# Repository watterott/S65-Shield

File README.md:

# S65-Shield
The S65-Shield is a plug-on module with color TFT-Display (176x132), microSD socket and rotary encoder for Arduino.

* Color-Display (176x132)
* Rotary-Encoder
* microSD Socket (SPI)
* Open-Source and released under the [Creative Commons Attribution Share-Alike License](https://creativecommons.org/licenses/by-sa/4.0/).
* **[Documentation on learn.watterott.com](https://learn.watterott.com)**

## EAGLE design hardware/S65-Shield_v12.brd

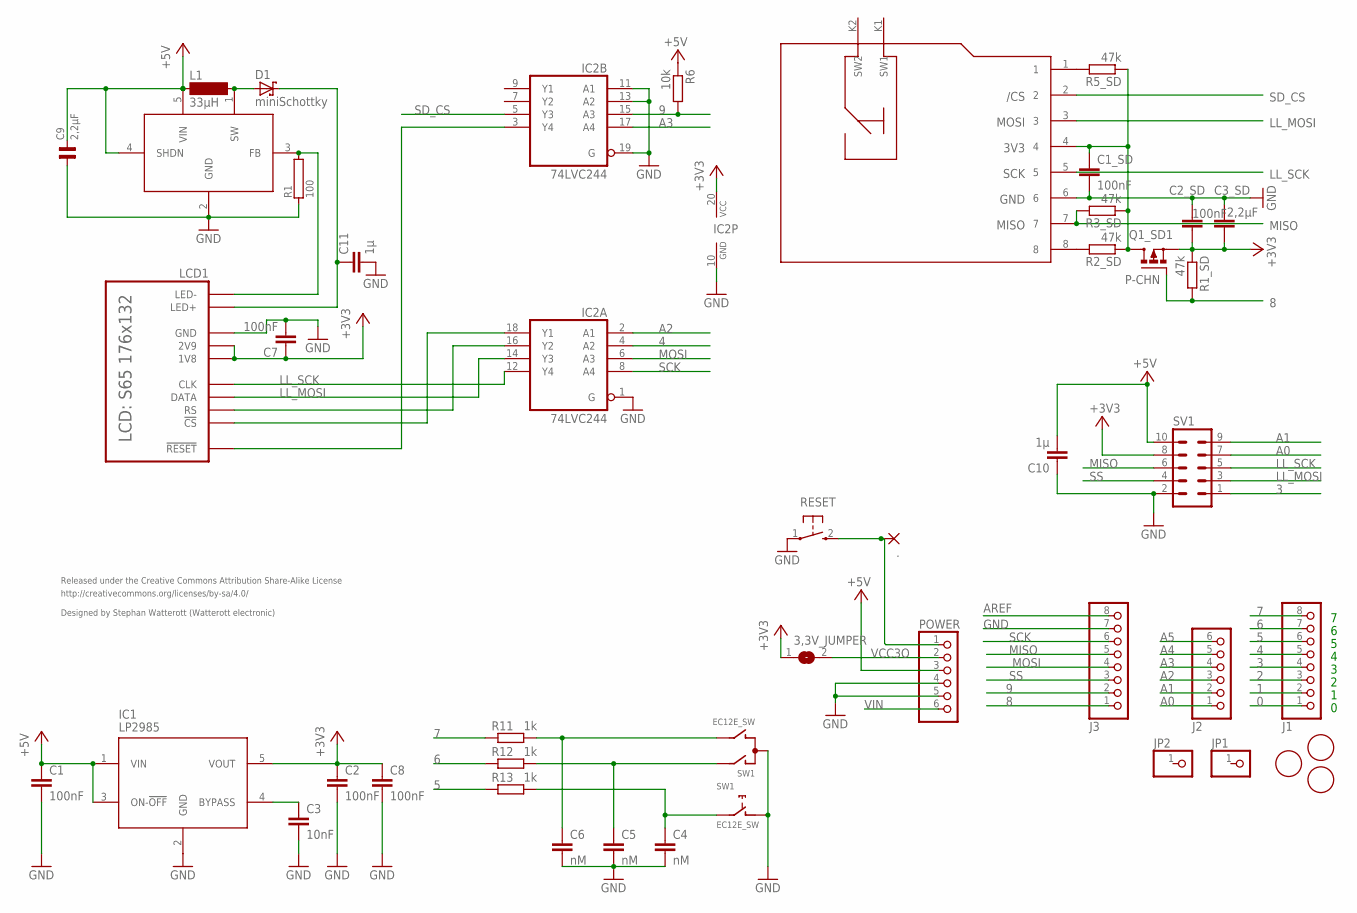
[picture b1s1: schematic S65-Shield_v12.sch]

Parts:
3,3V_JUMPER: SJ
.: SMD2; SMD1,27-2,54
C1, C1_SD, C2, C2_SD, C7: 100nF; C0603
C3: 10nF; C0603
C3_SD: 2,2µF; C0805
C4, C5, C6: nM; C0603
C8: 100nF; C0805
C9: 2,2µF; 0805
C10, C11: 1µ; C0603
D1: miniSchottky; D0603
IC1: LP2985; SOT23-5
IC2: 74LVC244; SO20W
J1, J3: PINHD-1X8; 1X08
J2: PINHD-1X6; 1X06
JP1, JP2: PINHD-1X1; 1X01
L1: 33µH; MS42
LCD1: S65
POWER: PINHD-1X6; 1X06
Q1_SD1: P-CHN; MICRO3
R1: 100; 0603
R1_SD, R2_SD, R3_SD, R5_SD: 47k; R0603
R6: 10k; R0603
R11, R12, R13: 1k; R0603
RESET: TAST_SMD1; SMD_TASTER
SD: MICRO-SD
SV1: ML10
SW1: EC12E_SW; ALPS_EC12E_SW
U$1, U$2, U$3: FIDUCIALMOUNT; FIDUCIA-MOUNT
U$4: LM2705; SOT23-5

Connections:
0: J1.1
1: J1.2
2: J1.3
3: J1.4, SV1.1
4: IC2.4 (A2), J1.5
5: J1.6, R13.1
6: J1.7, R12.1
7: J1.8, R11.1
8: J3.1, Q1_SD1.1 (G), R1_SD.2
9: IC2.15 (A3), J3.2, R6.2
+3V3: 3,3V_JUMPER.1, C2.1, C2_SD.2, C3_SD.2, C7.1, C8.1, IC1.5 (VOUT), IC2.20 (VCC), LCD1.1V8, LCD1.2V9, Q1_SD1.2 (S), R1_SD.1, SV1.8
+5V: C1.1, C9.2, C10.2, IC1.1 (VIN), IC1.3 (ON-!OFF), L1.1, POWER.3, R6.1, SV1.10, U$4.4 (SHDN), U$4.5 (VIN)
A0: J2.1, SV1.7
A1: J2.2, SV1.9
A2: IC2.2 (A1), J2.3
A3: IC2.17 (A4), J2.4
A4: J2.5
A5: J2.6
AREF: J3.8
GND: C1.2, C1_SD.2, C2.2, C2_SD.1, C3.2, C3_SD.1, C4.2, C5.2, C6.2, C7.2, C8.2, C9.1, C10.1, C11.2, IC1.2 (GND), IC2.1 (G), IC2.10 (GND), IC2.11 (A1), IC2.13 (A2), IC2.19 (G), J3.7, LCD1.GND, POWER.4, POWER.5, R1.1, RESET.1, SD.6, SV1.2, SW1.C, SW1.D (1), U$4.2 (GND)
LED+: C11.1, D1.1 (C), LCD1.LED+
LED-: LCD1.LED-, R1.2, U$4.3 (FB)
LL_MOSI: IC2.14 (Y3), LCD1.DATA, SD.3, SV1.3
LL_SCK: IC2.12 (Y4), LCD1.CLK, SD.5, SV1.5
MISO: J3.5, R3_SD.2, SD.7, SV1.6
MOSI: IC2.6 (A3), J3.4
unnamed: R5_SD.2, SD.1
unnamed: IC2.16 (Y2), LCD1.RS
unnamed: IC2.18 (Y1), LCD1.CS (!CS)
unnamed: IC2.3 (Y4), LCD1.RESET (!RESET)
unnamed: D1.2 (A), L1.2, U$4.1 (SW)
unnamed: C4.1, R13.2, SW1.E (2)
unnamed: C5.1, R12.2, SW1.A
unnamed: C6.1, R11.2, SW1.B
unnamed: C3.1, IC1.4 (BYPASS)
unnamed: ..1, POWER.1, RESET.2 (S)
unnamed: R2_SD.2, SD.8
SCK: IC2.8 (A4), J3.6
SD_3V3: C1_SD.1, Q1_SD1.3 (D), R2_SD.1, R3_SD.1, R5_SD.1, SD.4
SD_CS: IC2.5 (Y3), SD.2
SS: J3.3, SV1.4
VCC3O: 3,3V_JUMPER.2, POWER.2
VIN: POWER.6

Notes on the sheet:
Released under the Creative Commons Attribution Share-Alike License
http://creativecommons.org/licenses/by-sa/4.0/
Designed by Stephan Watterott (Watterott electronic)

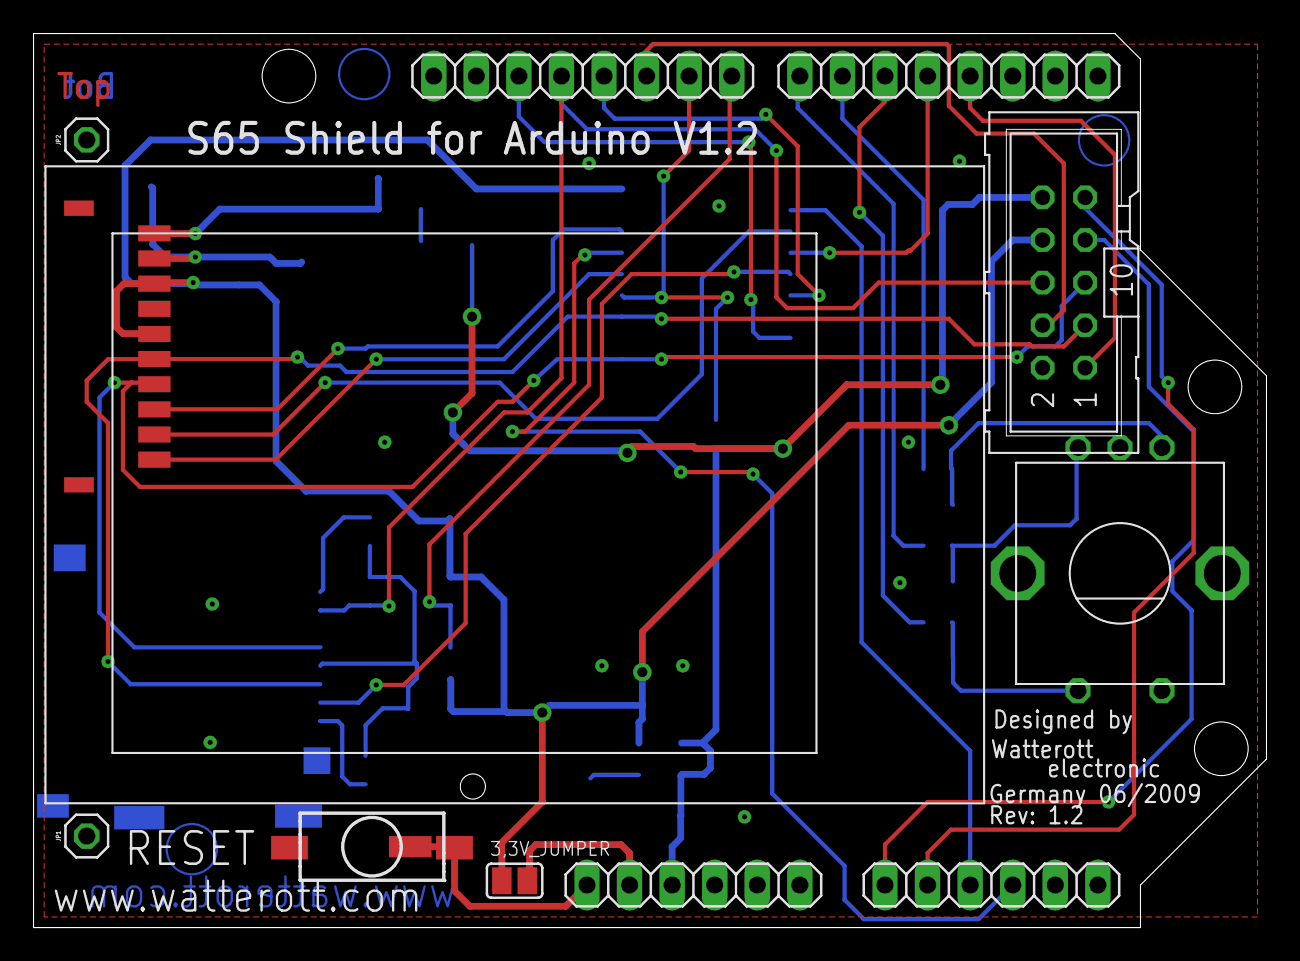
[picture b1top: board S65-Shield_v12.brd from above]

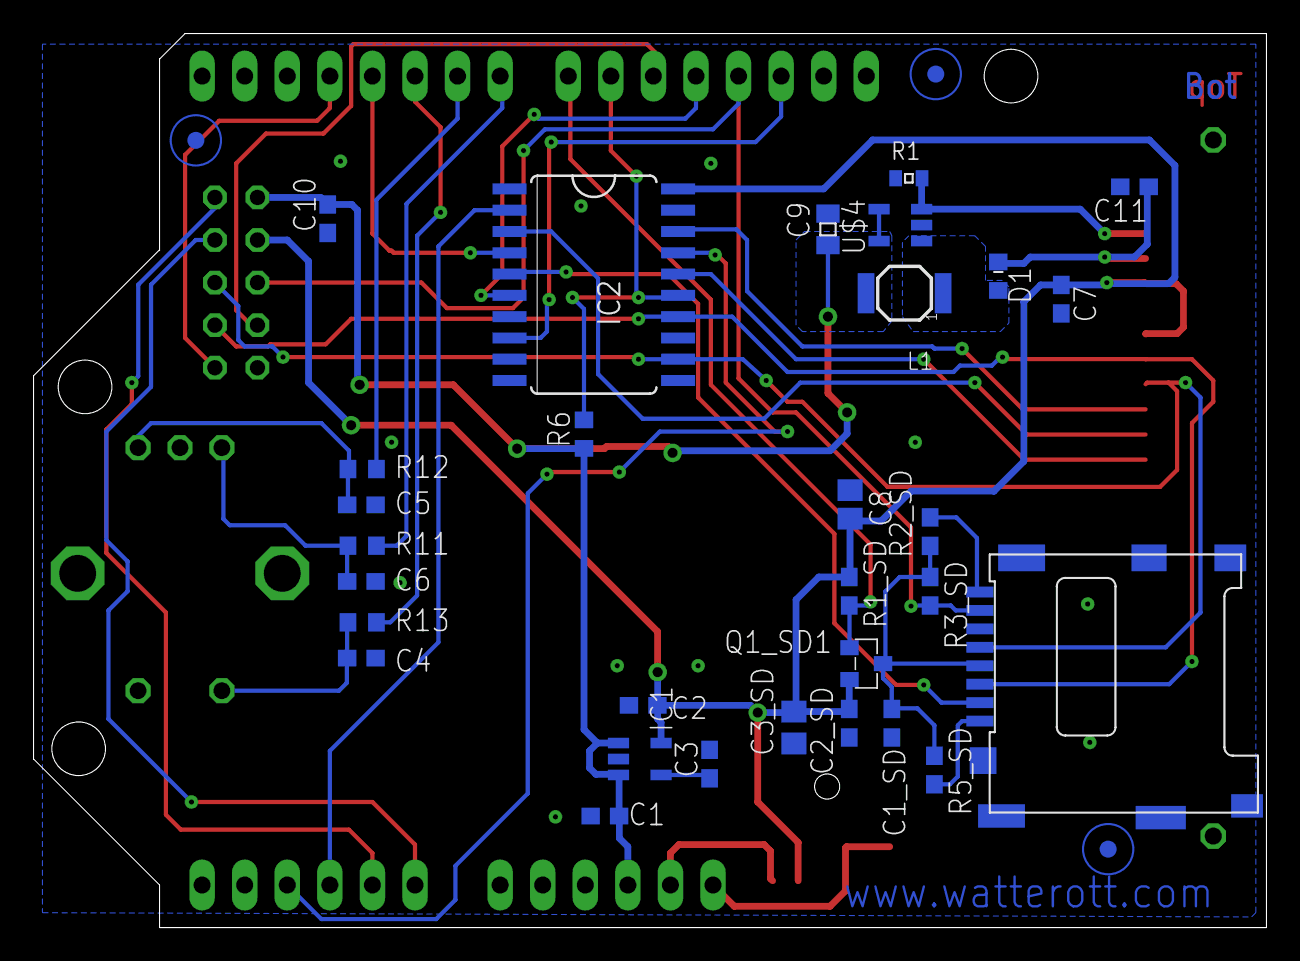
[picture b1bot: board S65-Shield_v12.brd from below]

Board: 2 copper layers, 73.6 x 53.3 mm, 45 parts (33 on the bottom side), 36 nets.
